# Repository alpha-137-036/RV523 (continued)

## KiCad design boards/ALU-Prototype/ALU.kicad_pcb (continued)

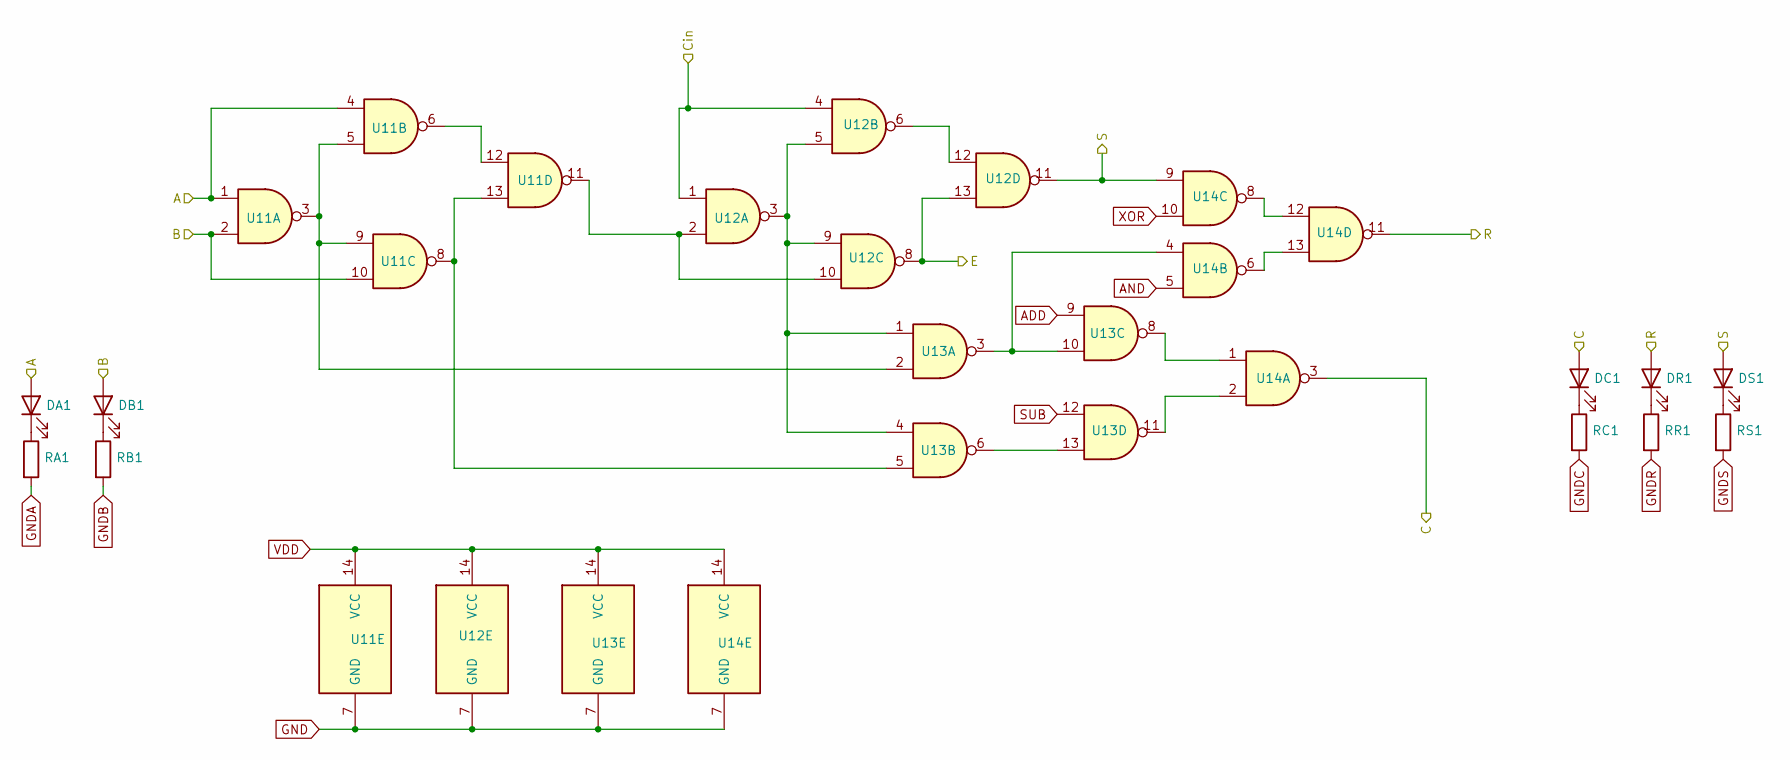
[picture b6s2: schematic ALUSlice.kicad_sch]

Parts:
DA1: LED_0402_1005Metric; LCSC C22355736
DB1: LED_0402_1005Metric; LCSC C22355736
DC1: LED_0402_1005Metric; LCSC C22355736
DR1: LED_0402_1005Metric; LCSC C22355736
DS1: LED_0402_1005Metric; LCSC C22355736
RA1: 330; R_0402_1005Metric; LCSC C12246
RB1: 330; R_0402_1005Metric; LCSC C12246
RC1: 330; R_0402_1005Metric; LCSC C12246
RR1: 330; R_0402_1005Metric; LCSC C12246
RS1: 330; R_0402_1005Metric; LCSC C12246
U11, U12, U13, U14: TSSOP-14_4.4x5mm_P0.65mm; LCSC C5587

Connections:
/ALUSlice0/C: U12.1, U12.4; also elsewhere on the board
/ALUSlice1/C: DC1.2 (A), U14.3; also elsewhere on the board
A1: DA1.2 (A), U11.1, U11.4; also elsewhere on the board
ADD: U13.9; also elsewhere on the board
AND: U14.5; also elsewhere on the board
B1: DB1.2 (A), U11.2, U11.10; also elsewhere on the board
E1: U12.8, U12.13; also elsewhere on the board
GND: U11.7 (GND), U12.7 (GND), U13.7 (GND), U14.7 (GND); also elsewhere on the board
GNDA: RA1.2; also elsewhere on the board
GNDB: RB1.2; also elsewhere on the board
GNDC: RC1.2; also elsewhere on the board
GNDR: RR1.2; also elsewhere on the board
GNDS: RS1.2; also elsewhere on the board
unnamed: DA1.1 (K), RA1.1
unnamed: DB1.1 (K), RB1.1
unnamed: DC1.1 (K), RC1.1
unnamed: DR1.1 (K), RR1.1
unnamed: DS1.1 (K), RS1.1
unnamed: U11.3, U11.5, U11.9, U13.2
unnamed: U11.11, U12.2, U12.10
unnamed: U11.6, U11.12
unnamed: U11.8, U11.13, U13.5
unnamed: U12.3, U12.5, U12.9, U13.1, U13.4
unnamed: U12.6, U12.12
unnamed: U13.8, U14.1
unnamed: U13.3, U13.10, U14.4
unnamed: U13.11, U14.2
unnamed: U13.6, U13.13
unnamed: U14.8, U14.12
unnamed: U14.6, U14.13
R1: DR1.2 (A), U14.11; also elsewhere on the board
S1: DS1.2 (A), U12.11, U14.9; also elsewhere on the board
SUB: U13.12; also elsewhere on the board
VDD: U11.14 (VCC), U12.14 (VCC), U13.14 (VCC), U14.14 (VCC); also elsewhere on the board
XOR: U14.10; also elsewhere on the board

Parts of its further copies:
DA0, DA2, DA3, DA4, DA5, DA6, DA7: LED_0402_1005Metric; LCSC C22355736
DB0, DB2, DB3, DB4, DB5, DB6, DB7: LED_0402_1005Metric; LCSC C22355736
DC0, DC2, DC3, DC4, DC5, DC6, DC7: LED_0402_1005Metric; LCSC C22355736
DR0, DR2, DR3, DR4, DR5, DR6, DR7: LED_0402_1005Metric; LCSC C22355736
DS0, DS2, DS3, DS4, DS5, DS6, DS7: LED_0402_1005Metric; LCSC C22355736
RA0, RA2, RA3, RA4, RA5, RA6, RA7: 330; R_0402_1005Metric; LCSC C12246
RB0, RB2, RB3, RB4, RB5, RB6, RB7: 330; R_0402_1005Metric; LCSC C12246
RC0, RC2, RC3, RC4, RC5, RC6, RC7: 330; R_0402_1005Metric; LCSC C12246
RR0, RR2, RR3, RR4, RR5, RR6, RR7: 330; R_0402_1005Metric; LCSC C12246
RS0, RS2, RS3, RS4, RS5, RS6, RS7: 330; R_0402_1005Metric; LCSC C12246
U01, U02, U03, U04, U21, U22, U23, U24, U31, U32, U33, U34, U41, U42, U43, U44, U51, U52, U53, U54, U61, U62, U63, U64, U71, U72, U73, U74: TSSOP-14_4.4x5mm_P0.65mm; LCSC C5587

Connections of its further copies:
/ALUSlice0/C: DC0.2 (A), U04.3; also elsewhere on the board
/ALUSlice0/R: DR0.2 (A), U04.11; also elsewhere on the board
/ALUSlice1/C: U22.1, U22.4; also elsewhere on the board
/ALUSlice2/C: DC2.2 (A), U24.3, U32.1, U32.4
/ALUSlice3/C: DC3.2 (A), U34.3, U42.1, U42.4
/ALUSlice4/C: DC4.2 (A), U44.3, U52.1, U52.4
/ALUSlice5/C: DC5.2 (A), U54.3, U62.1, U62.4
/ALUSlice6/C: DC6.2 (A), U64.3, U72.1, U72.4
A0: DA0.2 (A), U01.1, U01.4; also elsewhere on the board
A2: DA2.2 (A), U21.1, U21.4; also elsewhere on the board
A3: DA3.2 (A), U31.1, U31.4; also elsewhere on the board
A4: DA4.2 (A), U41.1, U41.4; also elsewhere on the board
A5: DA5.2 (A), U51.1, U51.4; also elsewhere on the board
A6: DA6.2 (A), U61.1, U61.4; also elsewhere on the board
A7: DA7.2 (A), U71.1, U71.4; also elsewhere on the board
ADD: U03.9, U23.9, U33.9, U43.9, U53.9, U63.9, U73.9; also elsewhere on the board
AND: U04.5, U24.5, U34.5, U44.5, U54.5, U64.5, U74.5; also elsewhere on the board
B0: DB0.2 (A), U01.2, U01.10; also elsewhere on the board
B2: DB2.2 (A), U21.2, U21.10; also elsewhere on the board
B3: DB3.2 (A), U31.2, U31.10; also elsewhere on the board
B4: DB4.2 (A), U41.2, U41.10; also elsewhere on the board
B5: DB5.2 (A), U51.2, U51.10; also elsewhere on the board
B6: DB6.2 (A), U61.2, U61.10; also elsewhere on the board
B7: DB7.2 (A), U71.2, U71.10; also elsewhere on the board
C: DC7.2 (A), U74.3; also elsewhere on the board
Cin: U02.1, U02.4; also elsewhere on the board
E0: U02.8, U02.13; also elsewhere on the board
E2: U22.8, U22.13; also elsewhere on the board
E3: U32.8, U32.13; also elsewhere on the board
E4: U42.8, U42.13; also elsewhere on the board
E5: U52.8, U52.13; also elsewhere on the board
E6: U62.8, U62.13; also elsewhere on the board
E7: U72.8, U72.13; also elsewhere on the board
GND: U01.7 (GND), U02.7 (GND), U03.7 (GND), U04.7 (GND), U21.7 (GND), U22.7 (GND), U23.7 (GND), U24.7 (GND), U31.7 (GND), U32.7 (GND), U33.7 (GND), U34.7 (GND), U41.7 (GND), U42.7 (GND), U43.7 (GND), U44.7 (GND), U51.7 (GND), U52.7 (GND), U53.7 (GND), U54.7 (GND), U61.7 (GND), U62.7 (GND), U63.7 (GND), U64.7 (GND), U71.7 (GND), U72.7 (GND), U73.7 (GND), U74.7 (GND); also elsewhere on the board
GNDA: RA0.2, RA2.2, RA3.2, RA4.2, RA5.2, RA6.2, RA7.2; also elsewhere on the board
GNDB: RB0.2, RB2.2, RB3.2, RB4.2, RB5.2, RB6.2, RB7.2; also elsewhere on the board
GNDC: RC0.2, RC2.2, RC3.2, RC4.2, RC5.2, RC6.2, RC7.2; also elsewhere on the board
GNDR: RR0.2, RR2.2, RR3.2, RR4.2, RR5.2, RR6.2, RR7.2; also elsewhere on the board
GNDS: RS0.2, RS2.2, RS3.2, RS4.2, RS5.2, RS6.2, RS7.2; also elsewhere on the board
unnamed: DA0.1 (K), RA0.1
unnamed: DA2.1 (K), RA2.1
unnamed: DA3.1 (K), RA3.1
unnamed: DA4.1 (K), RA4.1
unnamed: DA5.1 (K), RA5.1
unnamed: DA6.1 (K), RA6.1
unnamed: DA7.1 (K), RA7.1
unnamed: DB0.1 (K), RB0.1
unnamed: DB2.1 (K), RB2.1
unnamed: DB3.1 (K), RB3.1
unnamed: DB4.1 (K), RB4.1
unnamed: DB5.1 (K), RB5.1
unnamed: DB6.1 (K), RB6.1
unnamed: DB7.1 (K), RB7.1
unnamed: DC0.1 (K), RC0.1
unnamed: DC2.1 (K), RC2.1
unnamed: DC3.1 (K), RC3.1
unnamed: DC4.1 (K), RC4.1
unnamed: DC5.1 (K), RC5.1
unnamed: DC6.1 (K), RC6.1
unnamed: DC7.1 (K), RC7.1
unnamed: DR0.1 (K), RR0.1
unnamed: DR2.1 (K), RR2.1
unnamed: DR3.1 (K), RR3.1
unnamed: DR4.1 (K), RR4.1
unnamed: DR5.1 (K), RR5.1
unnamed: DR6.1 (K), RR6.1
unnamed: DR7.1 (K), RR7.1
unnamed: DS0.1 (K), RS0.1
unnamed: DS2.1 (K), RS2.1
unnamed: DS3.1 (K), RS3.1
unnamed: DS4.1 (K), RS4.1
unnamed: DS5.1 (K), RS5.1
unnamed: DS6.1 (K), RS6.1
unnamed: DS7.1 (K), RS7.1
unnamed: U01.3, U01.5, U01.9, U03.2
unnamed: U01.11, U02.2, U02.10
unnamed: U01.6, U01.12
unnamed: U01.8, U01.13, U03.5
unnamed: U02.3, U02.5, U02.9, U03.1, U03.4
unnamed: U02.6, U02.12
unnamed: U03.8, U04.1
unnamed: U03.3, U03.10, U04.4
unnamed: U03.11, U04.2
unnamed: U03.6, U03.13
unnamed: U04.8, U04.12
unnamed: U04.6, U04.13
unnamed: U21.3, U21.5, U21.9, U23.2
unnamed: U21.11, U22.2, U22.10
unnamed: U21.6, U21.12
unnamed: U21.8, U21.13, U23.5
unnamed: U22.3, U22.5, U22.9, U23.1, U23.4
unnamed: U22.6, U22.12
unnamed: U23.8, U24.1
unnamed: U23.3, U23.10, U24.4
unnamed: U23.11, U24.2
unnamed: U23.6, U23.13
unnamed: U24.8, U24.12
unnamed: U24.6, U24.13
unnamed: U31.3, U31.5, U31.9, U33.2
unnamed: U31.11, U32.2, U32.10
unnamed: U31.6, U31.12
unnamed: U31.8, U31.13, U33.5
unnamed: U32.3, U32.5, U32.9, U33.1, U33.4
unnamed: U32.6, U32.12
unnamed: U33.8, U34.1
unnamed: U33.3, U33.10, U34.4
unnamed: U33.11, U34.2
unnamed: U33.6, U33.13
unnamed: U34.8, U34.12
unnamed: U34.6, U34.13
unnamed: U41.3, U41.5, U41.9, U43.2
unnamed: U41.11, U42.2, U42.10
unnamed: U41.6, U41.12
unnamed: U41.8, U41.13, U43.5
unnamed: U42.3, U42.5, U42.9, U43.1, U43.4
unnamed: U42.6, U42.12
unnamed: U43.8, U44.1
unnamed: U43.3, U43.10, U44.4
unnamed: U43.11, U44.2
unnamed: U43.6, U43.13
unnamed: U44.8, U44.12
unnamed: U44.6, U44.13
unnamed: U51.3, U51.5, U51.9, U53.2
unnamed: U51.11, U52.2, U52.10
unnamed: U51.6, U51.12
unnamed: U51.8, U51.13, U53.5
unnamed: U52.3, U52.5, U52.9, U53.1, U53.4
unnamed: U52.6, U52.12
unnamed: U53.8, U54.1
unnamed: U53.3, U53.10, U54.4
unnamed: U53.11, U54.2
unnamed: U53.6, U53.13
unnamed: U54.8, U54.12
unnamed: U54.6, U54.13
unnamed: U61.3, U61.5, U61.9, U63.2
unnamed: U61.11, U62.2, U62.10
unnamed: U61.6, U61.12
unnamed: U61.8, U61.13, U63.5
unnamed: U62.3, U62.5, U62.9, U63.1, U63.4
unnamed: U62.6, U62.12
unnamed: U63.8, U64.1
unnamed: U63.3, U63.10, U64.4
unnamed: U63.11, U64.2
unnamed: U63.6, U63.13
unnamed: U64.8, U64.12
unnamed: U64.6, U64.13
unnamed: U71.3, U71.5, U71.9, U73.2
unnamed: U71.11, U72.2, U72.10
unnamed: U71.6, U71.12
unnamed: U71.8, U71.13, U73.5
unnamed: U72.3, U72.5, U72.9, U73.1, U73.4
unnamed: U72.6, U72.12
unnamed: U73.8, U74.1
unnamed: U73.3, U73.10, U74.4
unnamed: U73.11, U74.2
unnamed: U73.6, U73.13
unnamed: U74.8, U74.12
unnamed: U74.6, U74.13
R2: DR2.2 (A), U24.11; also elsewhere on the board
R3: DR3.2 (A), U34.11; also elsewhere on the board
R4: DR4.2 (A), U44.11; also elsewhere on the board
R5: DR5.2 (A), U54.11; also elsewhere on the board
R6: DR6.2 (A), U64.11; also elsewhere on the board
R7: DR7.2 (A), U74.11; also elsewhere on the board
S0: DS0.2 (A), U02.11, U04.9; also elsewhere on the board
S2: DS2.2 (A), U22.11, U24.9; also elsewhere on the board
S3: DS3.2 (A), U32.11, U34.9; also elsewhere on the board
S4: DS4.2 (A), U42.11, U44.9; also elsewhere on the board
S5: DS5.2 (A), U52.11, U54.9; also elsewhere on the board
S6: DS6.2 (A), U62.11, U64.9; also elsewhere on the board
S7: DS7.2 (A), U72.11, U74.9; also elsewhere on the board
SUB: U03.12, U23.12, U33.12, U43.12, U53.12, U63.12, U73.12; also elsewhere on the board
VDD: U01.14 (VCC), U02.14 (VCC), U03.14 (VCC), U04.14 (VCC), U21.14 (VCC), U22.14 (VCC), U23.14 (VCC), U24.14 (VCC), U31.14 (VCC), U32.14 (VCC), U33.14 (VCC), U34.14 (VCC), U41.14 (VCC), U42.14 (VCC), U43.14 (VCC), U44.14 (VCC), U51.14 (VCC), U52.14 (VCC), U53.14 (VCC), U54.14 (VCC), U61.14 (VCC), U62.14 (VCC), U63.14 (VCC), U64.14 (VCC), U71.14 (VCC), U72.14 (VCC), U73.14 (VCC), U74.14 (VCC); also elsewhere on the board
XOR: U04.10, U24.10, U34.10, U44.10, U54.10, U64.10, U74.10; also elsewhere on the board

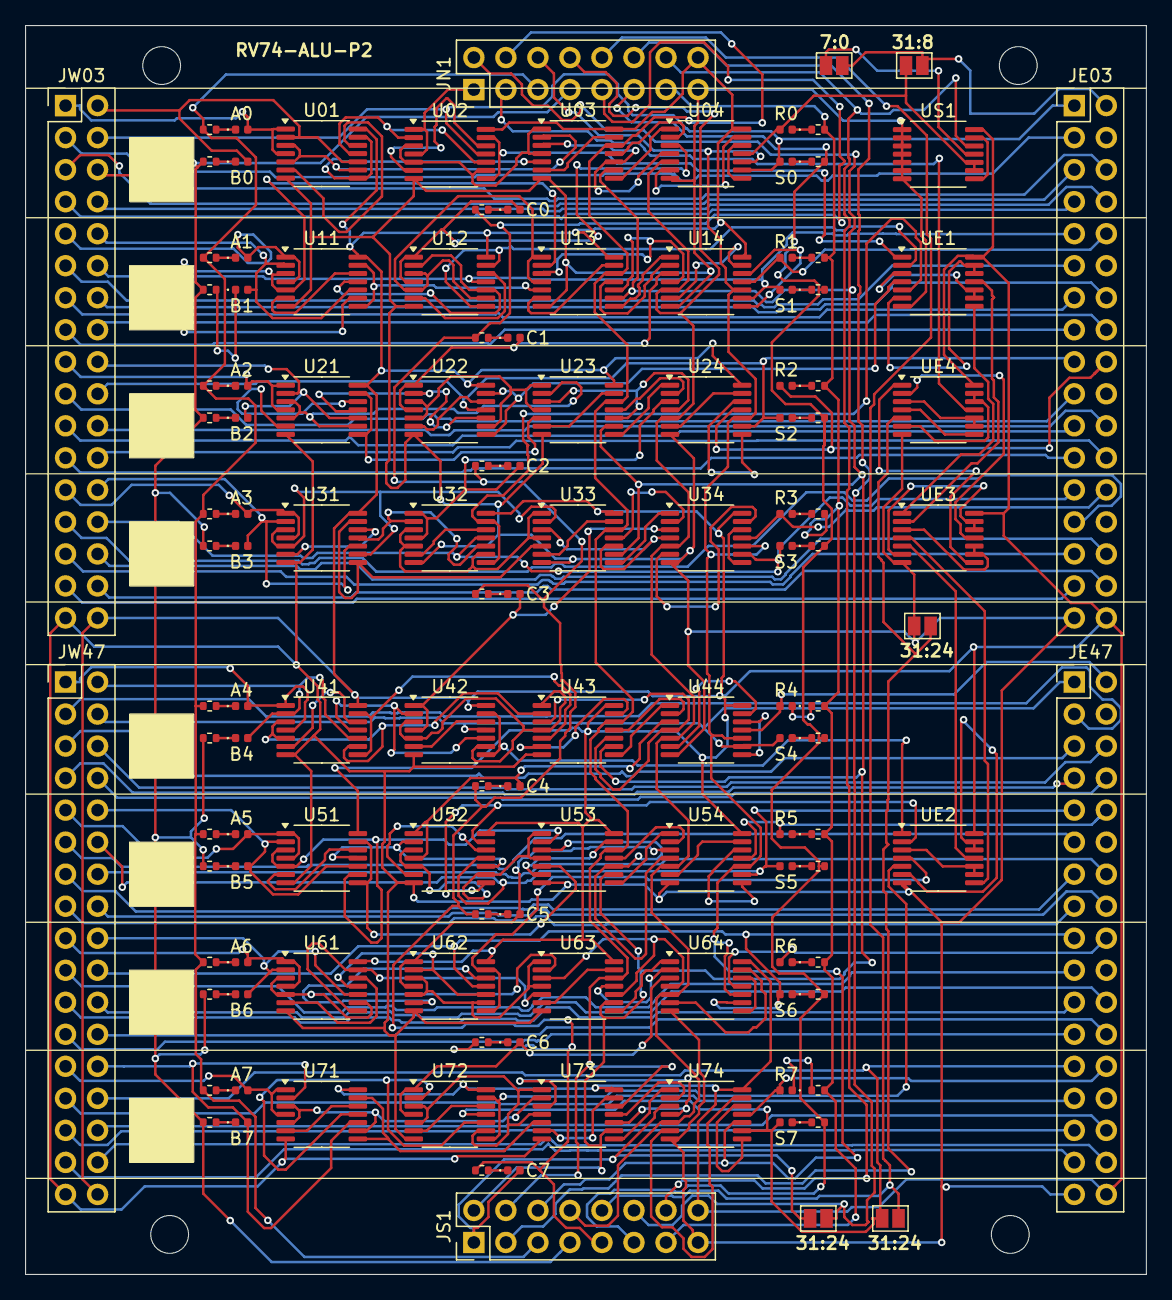
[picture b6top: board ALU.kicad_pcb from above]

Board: 2 copper layers, 88.9 x 99.1 mm, 128 parts (0 on the bottom side), 259 nets.

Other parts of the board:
JPE32: SolderJumper-2_P1.3mm_Open_Pad1.0x1.5mm
JPX0: SolderJumper-2_P1.3mm_Open_Pad1.0x1.5mm
JPXN0: SolderJumper-2_P1.3mm_Open_Pad1.0x1.5mm
US1: TSSOP-14_4.4x5mm_P0.65mm

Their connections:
!SET0: US1.12; also elsewhere on the board
/ALUSlice0/R: JPXN0.1 (A), US1.9, US1.10; also elsewhere on the board
Ein: JPE32.2 (B); also elsewhere on the board
GND: JPE32.1 (A), US1.1, US1.2, US1.3, US1.4, US1.5, US1.6, US1.7 (GND); also elsewhere on the board
unnamed: JPX0.1 (A), US1.11
unnamed: US1.8, US1.13
R0: JPX0.2 (B), JPXN0.2 (B); also elsewhere on the board
VDD: US1.14 (VCC); also elsewhere on the board

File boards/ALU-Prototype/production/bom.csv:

Designator,Footprint,Quantity,Value,LCSC Part #
"DA0, DA1, DA2, DA3, DA4, DA5, DA6, DA7, DB0, DB1, DB2, DB3, DB4, DB5, DB6, DB7, DC0, DC1, DC2, DC3, DC4, DC5, DC6, DC7, DR0, DR1, DR2, DR3, DR4, DR5, DR6, DR7, DS0, DS1, DS2, DS3, DS4, DS5, DS6, DS7",0402,40,~,C22355736
"RA0, RA1, RA2, RA3, RA4, RA5, RA6, RA7, RB0, RB1, RB2, RB3, RB4, RB5, RB6, RB7, RC0, RC1, RC2, RC3, RC4, RC5, RC6, RC7, RR0, RR1, RR2, RR3, RR4, RR5, RR6, RR7, RS0, RS1, RS2, RS3, RS4, RS5, RS6, RS7",0402,40,330,C12246
"U01, U02, U03, U04, U11, U12, U13, U14, U21, U22, U23, U24, U31, U32, U33, U34, U41, U42, U43, U44, U51, U52, U53, U54, U61, U62, U63, U64, U71, U72, U73, U74",TSSOP-14_4.4x5mm_P0.65mm,32,~,C5587
